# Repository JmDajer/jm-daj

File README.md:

# Ortholinear keyboard
## Software
KiCad - https://www.kicad.org/download/

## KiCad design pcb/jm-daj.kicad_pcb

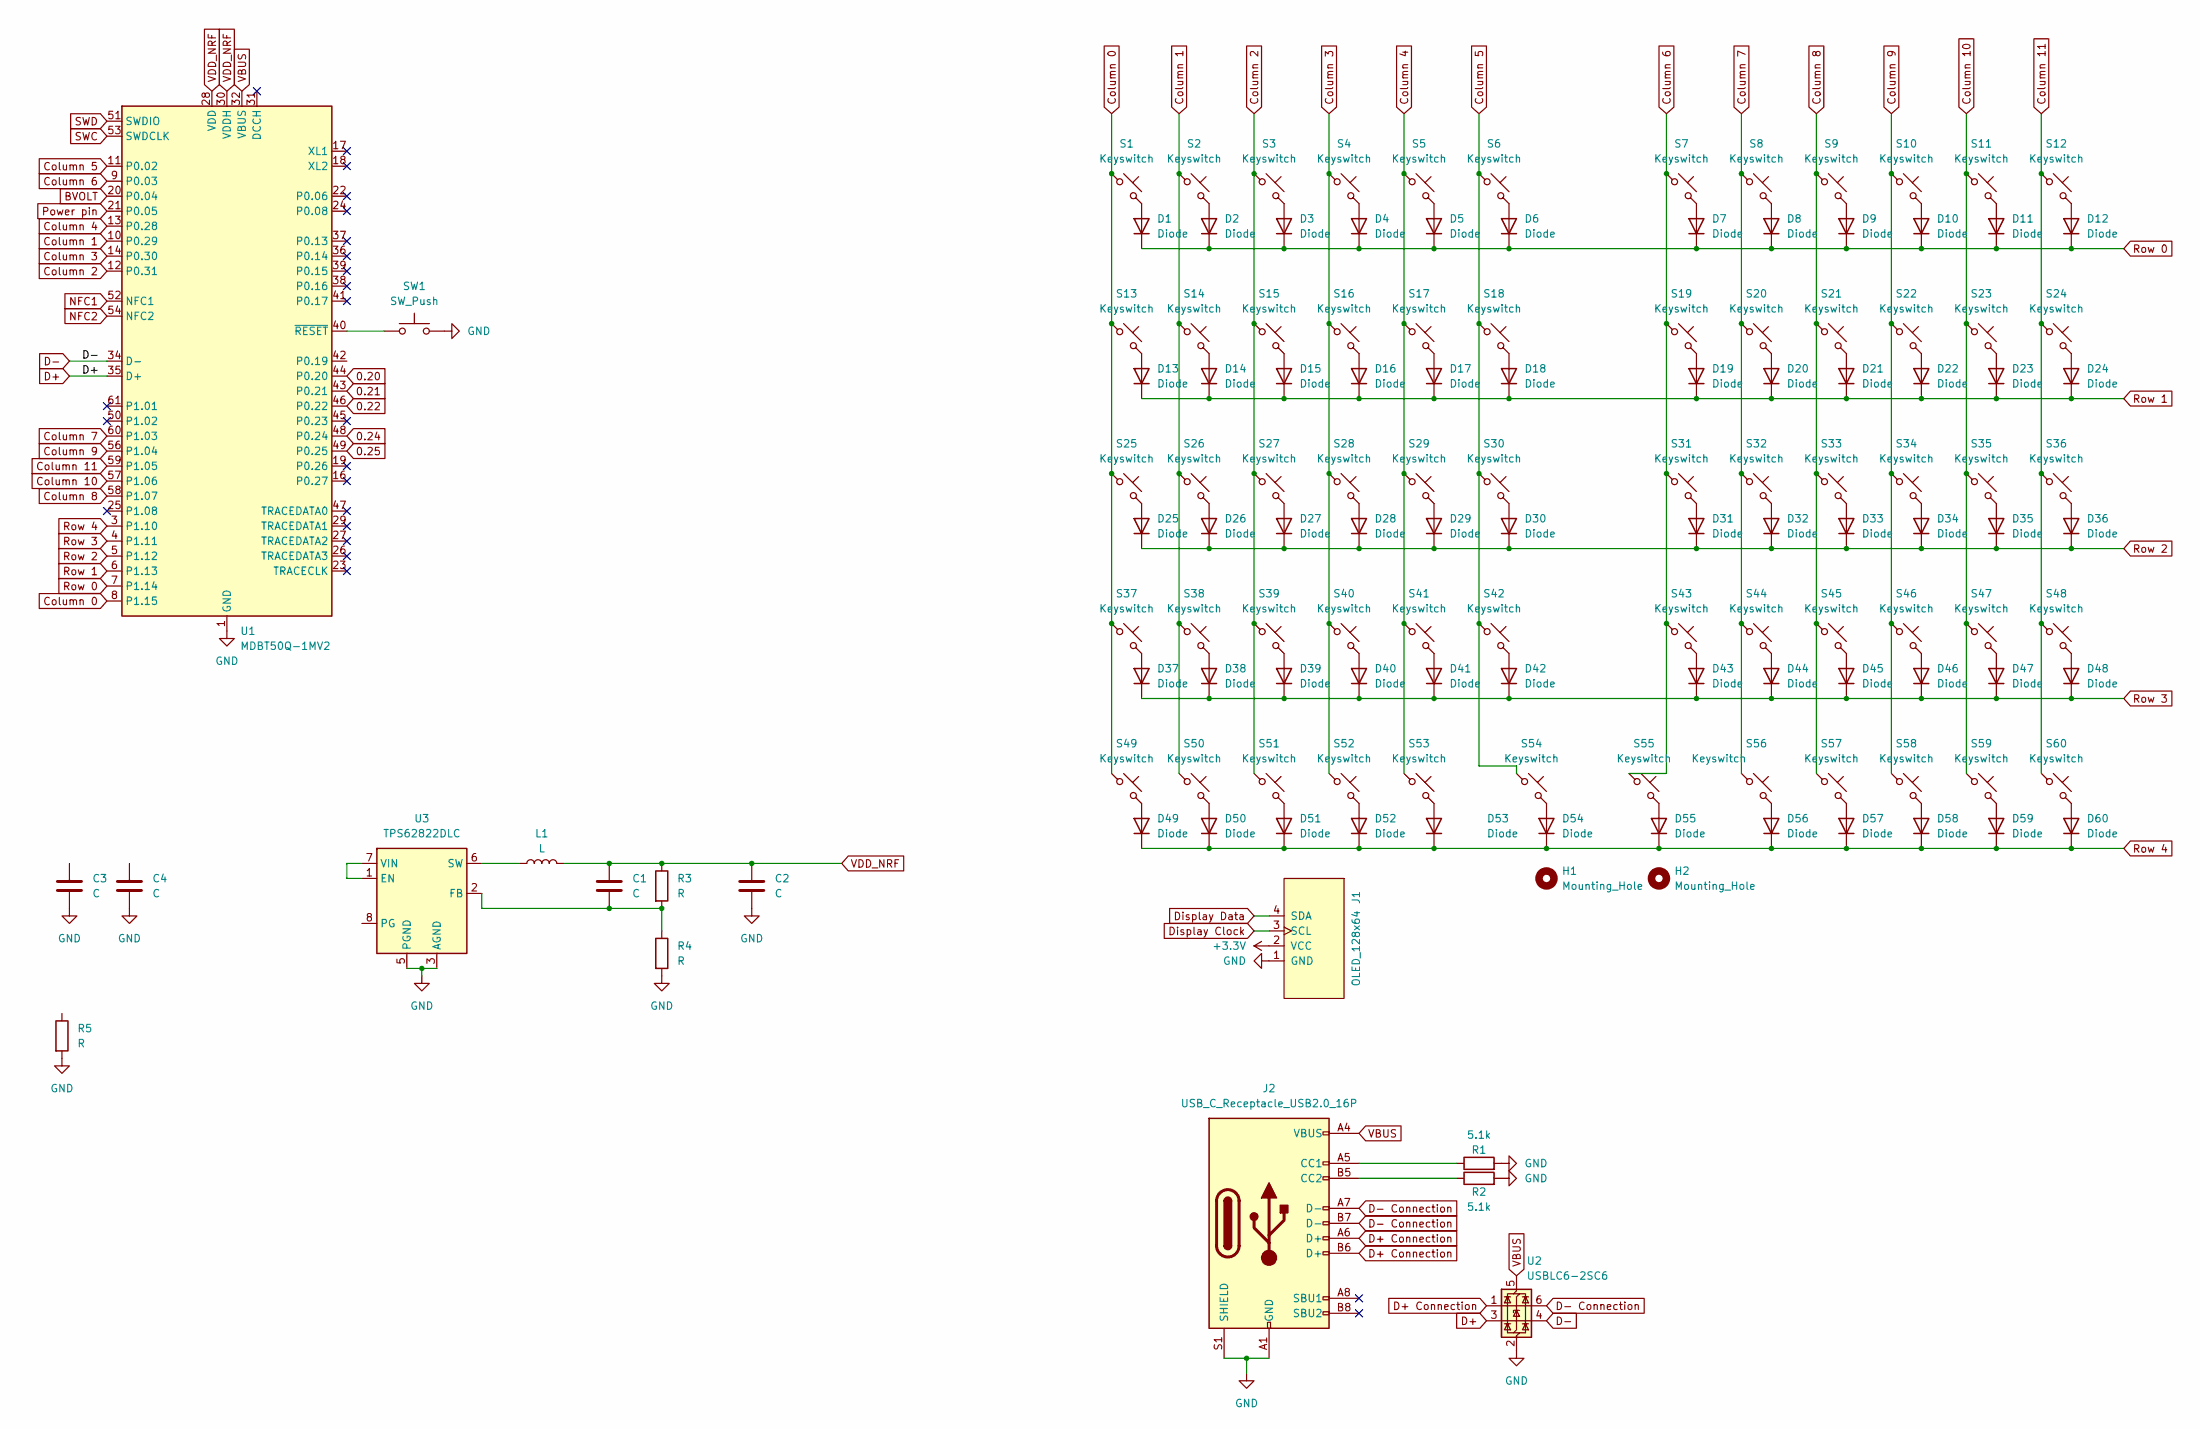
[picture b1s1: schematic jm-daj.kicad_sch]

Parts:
C1, C2, C3, C4: C
D1, D2, D3, D4, D5, D6, D7, D8, D9, D10, D11, D12, D13, D14, D15, D16, D17, D18, D19, D20, D21, D22, D23, D24, D25, D26, D27, D28, D29, D30, D31, D32, D33, D34, D35, D36, D37, D38, D39, D40, D41, D42, D43, D44, D45, D46, D47, D48, D49, D50, D51, D52, D53, D54, D55, D56, D57, D58, D59, D60: Diode; Diode_SOD-123
H1, H2: Mounting_Hole; Stabilizer_MX_2.00u
J1: OLED_128x64
J2: USB_C_Receptacle_USB2.0_16P
L1: L
R1, R2: 5.1k
R3, R4, R5: R
S1, S2, S3, S4, S5, S6, S7, S8, S9, S10, S11, S12, S13, S14, S15, S16, S17, S18, S19, S20, S21, S22, S23, S24, S25, S26, S27, S28, S29, S30, S31, S32, S33, S34, S35, S36, S37, S38, S39, S40, S41, S42, S43, S44, S45, S46, S47, S48, S49, S50, S51, S52, S53, S56, S57, S58, S59, S60: Keyswitch; Hotswap_MX_1.00u
S54, S55: Keyswitch; Hotswap_MX_2.00u
SW1: SW_Push; SW_Push_2P2T_Vertical_E-Switch_800UDP8P1A1M6
U1: MDBT50Q-1MV2; Raytac_MDBT50Q
U2: USBLC6-2SC6; SOT-23-6
U3: TPS62822DLC; Texas_VSON-HR-8_1.5x2mm_P0.5mm

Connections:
0.20: U1.44 (P0.20)
0.21: U1.43 (P0.21)
0.22: U1.46 (P0.22)
0.24: U1.48 (P0.24)
0.25: U1.49 (P0.25)
+3.3V: J1.2 (VCC)
BVOLT: U1.20 (P0.04)
Column 0: S1.1, S13.1, S25.1, S37.1, S49.1, U1.8 (P1.15)
Column 1: S2.1, S14.1, S26.1, S38.1, S50.1, U1.10 (P0.29)
Column 2: S3.1, S15.1, S27.1, S39.1, S51.1, U1.12 (P0.31)
Column 3: S4.1, S16.1, S28.1, S40.1, S52.1, U1.14 (P0.30)
Column 4: S5.1, S17.1, S29.1, S41.1, S53.1, U1.13 (P0.28)
Column 5: S6.1, S18.1, S30.1, S42.1, S54.1, U1.11 (P0.02)
Column 6: S7.1, S19.1, S31.1, S43.1, S55.1, U1.9 (P0.03)
Column 7: S8.1, S20.1, S32.1, S44.1, S56.1, U1.60 (P1.03)
Column 8: S9.1, S21.1, S33.1, S45.1, S57.1, U1.58 (P1.07)
Column 9: S10.1, S22.1, S34.1, S46.1, S58.1, U1.56 (P1.04)
Column 10: S11.1, S23.1, S35.1, S47.1, S59.1, U1.57 (P1.06)
Column 11: S12.1, S24.1, S36.1, S48.1, S60.1, U1.59 (P1.05)
D+: U1.35 (D+), U2.3 (I/O2)
D+ Connection: J2.A6 (D+), J2.B6 (D+), U2.1 (I/O1)
D-: U1.34 (D-), U2.4 (I/O2)
D- Connection: J2.A7 (D-), J2.B7 (D-), U2.6 (I/O1)
Display Clock: J1.3 (SCL)
Display Data: J1.4 (SDA)
GND: C2.2, C3.2, C4.2, J1.1 (GND), J2.A1 (GND), J2.A12 (GND), J2.B1 (GND), J2.B12 (GND), J2.S1 (SHIELD), R1.2, R2.2, R4.2, R5.2, SW1.2, U1.1 (GND), U1.2 (GND), U1.15 (GND), U1.33 (GND), U1.55 (GND), U2.2 (GND), U3.3 (AGND), U3.5 (PGND)
NFC1: U1.52 (NFC1)
NFC2: U1.54 (NFC2)
unnamed: C1.2, R3.2, R4.1, U3.2 (FB)
unnamed: D1.2 (A), S1.2
unnamed: D2.2 (A), S2.2
unnamed: D3.2 (A), S3.2
unnamed: D4.2 (A), S4.2
unnamed: D5.2 (A), S5.2
unnamed: D6.2 (A), S6.2
unnamed: D7.2 (A), S7.2
unnamed: D8.2 (A), S8.2
unnamed: D9.2 (A), S9.2
unnamed: D10.2 (A), S10.2
unnamed: D11.2 (A), S11.2
unnamed: D12.2 (A), S12.2
unnamed: D13.2 (A), S13.2
unnamed: D14.2 (A), S14.2
unnamed: D15.2 (A), S15.2
unnamed: D16.2 (A), S16.2
unnamed: D17.2 (A), S17.2
unnamed: D18.2 (A), S18.2
unnamed: D19.2 (A), S19.2
unnamed: D20.2 (A), S20.2
unnamed: D21.2 (A), S21.2
unnamed: D22.2 (A), S22.2
unnamed: D23.2 (A), S23.2
unnamed: D24.2 (A), S24.2
unnamed: D25.2 (A), S25.2
unnamed: D26.2 (A), S26.2
unnamed: D27.2 (A), S27.2
unnamed: D28.2 (A), S28.2
unnamed: D29.2 (A), S29.2
unnamed: D30.2 (A), S30.2
unnamed: D31.2 (A), S31.2
unnamed: D32.2 (A), S32.2
unnamed: D33.2 (A), S33.2
unnamed: D34.2 (A), S34.2
unnamed: D35.2 (A), S35.2
unnamed: D36.2 (A), S36.2
unnamed: D37.2 (A), S37.2
unnamed: D38.2 (A), S38.2
unnamed: D39.2 (A), S39.2
unnamed: D40.2 (A), S40.2
unnamed: D41.2 (A), S41.2
unnamed: D42.2 (A), S42.2
unnamed: D43.2 (A), S43.2
unnamed: D44.2 (A), S44.2
unnamed: D45.2 (A), S45.2
unnamed: D46.2 (A), S46.2
unnamed: D47.2 (A), S47.2
unnamed: D48.2 (A), S48.2
unnamed: D49.2 (A), S49.2
unnamed: D50.2 (A), S50.2
unnamed: D51.2 (A), S51.2
unnamed: D52.2 (A), S52.2
unnamed: D53.2 (A), S53.2
unnamed: D54.2 (A), S54.2
unnamed: D55.2 (A), S55.2
unnamed: D56.2 (A), S56.2
unnamed: D57.2 (A), S57.2
unnamed: D58.2 (A), S58.2
unnamed: D59.2 (A), S59.2
unnamed: D60.2 (A), S60.2
unnamed: J2.A5 (CC1), R1.1
unnamed: J2.B5 (CC2), R2.1
unnamed: L1.1, U3.6 (SW)
unnamed: SW1.1, U1.40 (~RESET)
unnamed: U3.1 (EN), U3.7 (VIN)
Power pin: U1.21 (P0.05)
Row 0: D1.1 (K), D2.1 (K), D3.1 (K), D4.1 (K), D5.1 (K), D6.1 (K), D7.1 (K), D8.1 (K), D9.1 (K), D10.1 (K), D11.1 (K), D12.1 (K), U1.7 (P1.14)
Row 1: D13.1 (K), D14.1 (K), D15.1 (K), D16.1 (K), D17.1 (K), D18.1 (K), D19.1 (K), D20.1 (K), D21.1 (K), D22.1 (K), D23.1 (K), D24.1 (K), U1.6 (P1.13)
Row 2: D25.1 (K), D26.1 (K), D27.1 (K), D28.1 (K), D29.1 (K), D30.1 (K), D31.1 (K), D32.1 (K), D33.1 (K), D34.1 (K), D35.1 (K), D36.1 (K), U1.5 (P1.12)
Row 3: D37.1 (K), D38.1 (K), D39.1 (K), D40.1 (K), D41.1 (K), D42.1 (K), D43.1 (K), D44.1 (K), D45.1 (K), D46.1 (K), D47.1 (K), D48.1 (K), U1.4 (P1.11)
Row 4: D49.1 (K), D50.1 (K), D51.1 (K), D52.1 (K), D53.1 (K), D54.1 (K), D55.1 (K), D56.1 (K), D57.1 (K), D58.1 (K), D59.1 (K), D60.1 (K), U1.3 (P1.10)
SWC: U1.53 (SWDCLK)
SWD: U1.51 (SWDIO)
VBUS: J2.A4 (VBUS), J2.A9 (VBUS), J2.B4 (VBUS), J2.B9 (VBUS), U1.32 (VBUS), U2.5 (VBUS)
VDD_NRF: C1.1, C2.1, L1.2, R3.1, U1.28 (VDD), U1.30 (VDDH)

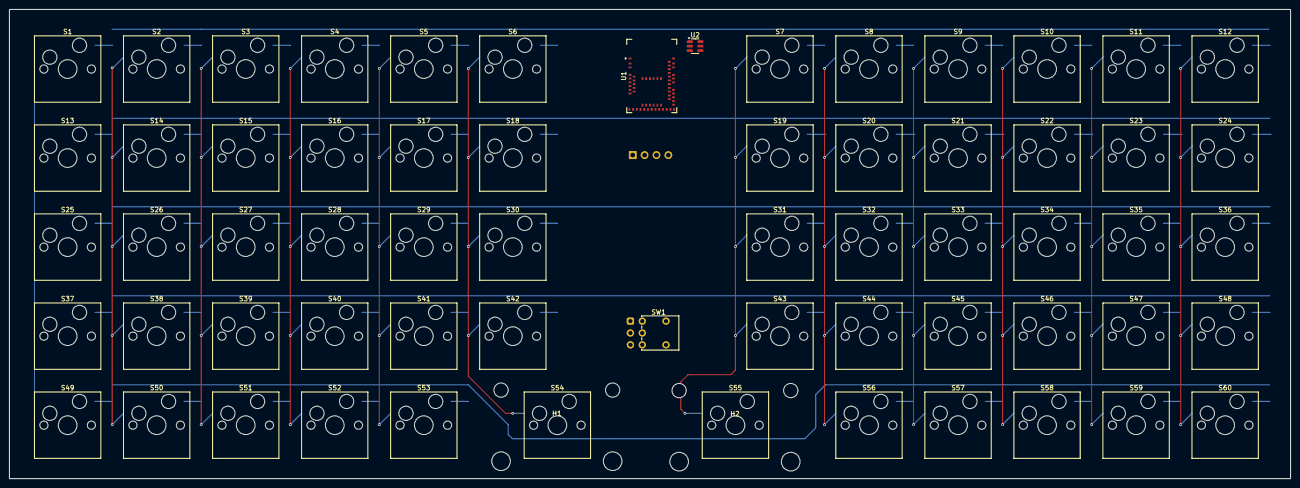
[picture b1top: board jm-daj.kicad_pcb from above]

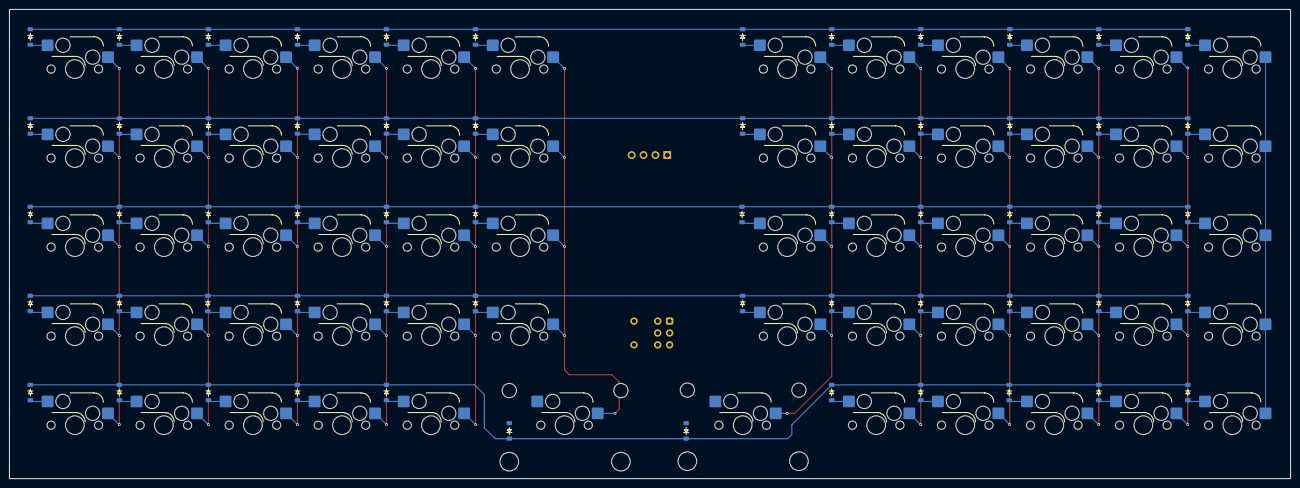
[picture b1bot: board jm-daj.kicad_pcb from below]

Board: 2 copper layers, 274.1 x 100.4 mm, 126 parts (60 on the bottom side), 83 nets.

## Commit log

2025-08-02 Add inital pcb directory and project
2025-08-02 Update schema and add ScottoKicad addons
2025-08-03 Finish matrix
